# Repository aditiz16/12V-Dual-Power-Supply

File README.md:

<!-- Project Title -->

# 12V Dual Power Supply Circuit and PCB Design

<!-- Project Description -->

# Description

The **12V Dual Power Supply** is an electronic device that provides reliable and regulated power to various electronic circuits and components. It offers two independent 12V output channels, making it particularly usefeul for wide range of applications.

<!-- Table of Contents -->

## Table of Contents

- [Features](#features)
- [Applications](#applications)
<!-- - [Schematic in KiCad](#schematic)-->

<!-- Features -->

## Features

- Dual Output Channels :
  The power supply features two separate 12-volt output channels that can be controlled independently. This allows you to power two different circuits or components simultaneously, each with its own voltage and current requirements.
- Regulated Voltage :
  The output voltage is accurately regulated to provide a stable 12-volt supply, ensuring that the connected devices receive consistent power levels. This is crucial for the proper functioning of sensitive electronic components.

<!-- Applications -->

## Applications

- Electronics Prototyping
- Testing and Debugging
- Audio and Amplifier Systems:
  Many audio circuits and amplifiers require a stable 12-volt power supply. The dual channels can power both the audio input stage and the amplifier stage separately.

<!-- Schematic -->
<!--## Schematic
-->

The 12V Dual Power Supply simplifies the process of powering and testing electronic circuits, offering stability, flexibility, and protection for a wide range of applications.

## Schematic

## PCB Layout

Check out the whole project in the PCB files of this Repository !

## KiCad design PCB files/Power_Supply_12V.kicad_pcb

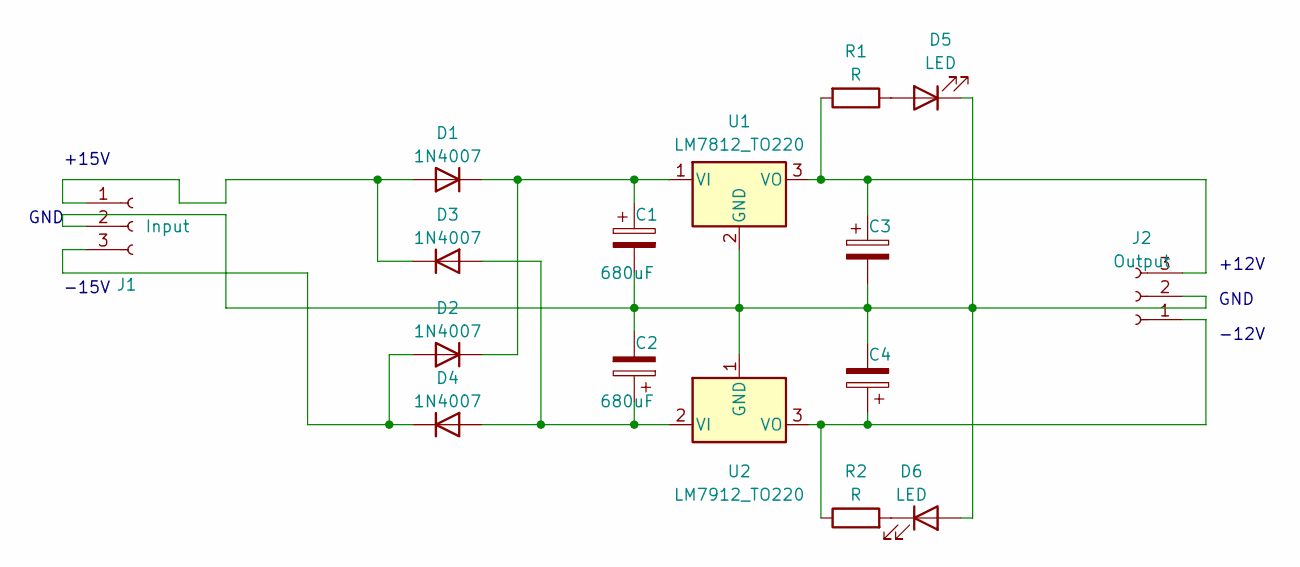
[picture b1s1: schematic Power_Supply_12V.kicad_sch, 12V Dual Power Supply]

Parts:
C1, C2: 680uF; CP_Radial_D10.0mm_P5.00mm
C3, C4: CP_Radial_D10.0mm_P5.00mm
D1, D2, D3, D4: 1N4007; D_DO-41_SOD81_P10.16mm_Horizontal
D5, D6: LED; LED_D3.0mm
J1: Input; TerminalBlock_Phoenix_MKDS-1,5-3-5.08_1x03_P5.08mm_Horizont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
J2: Output; TerminalBlock_Phoenix_MKDS-1,5-3-5.08_1x03_P5.08mm_Horizont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
R1, R2: R; R_Axial_DIN0204_L3.6mm_D1.6mm_P5.08mm_Horizontal
U1: LM7812_TO220; TO-220-3_Vertical
U2: LM7912_TO220; TO-220-3_Vertical

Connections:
unnamed: D1.2 (A), D3.1 (K), J1.1
unnamed: C1.1, D1.1 (K), D2.1 (K), U1.1 (VI)
unnamed: D2.2 (A), D4.1 (K), J1.3
unnamed: C2.1, D3.2 (A), D4.2 (A), U2.2 (VI)
unnamed: D5.2 (A), R1.1
unnamed: C1.2, C2.2, C3.2, C4.2, D5.1 (K), D6.2 (A), J1.2, J2.2, U1.2 (GND), U2.1 (GND)
unnamed: D6.1 (K), R2.2
unnamed: C4.1, J2.1, R2.1, U2.3 (VO)
unnamed: C3.1, J2.3, R1.2, U1.3 (VO)

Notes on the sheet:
+12V
-15V
GND
-12V
+15V

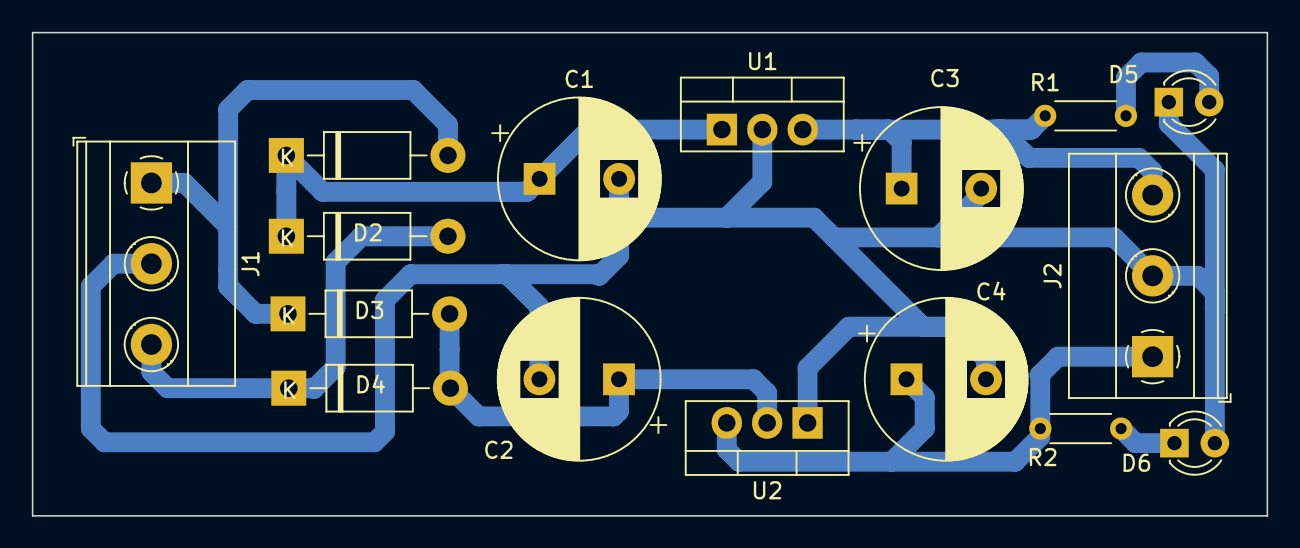
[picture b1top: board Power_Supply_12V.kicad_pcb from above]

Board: 2 copper layers, 77.6 x 30.4 mm, 16 parts (0 on the bottom side), 9 nets.

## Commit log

2023-08-16 Commit 1 - Schematic and PCB
2023-08-19 Added components and footprints
2023-08-19 Routing done
2023-08-22 Changes in trace width
2023-08-24 Changes in files
2023-08-28 Changed track width
2023-08-28 Created new files
2023-08-28 Changed Read me
